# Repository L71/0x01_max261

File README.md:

0x01_max261
===========

This Maxim Max261 based Eurorack filter module is making this filter IC useful
for audio processing in a standard 16HP Eurorack synth module. 
The IC is a dual filter and each filter is independently controlled using front
panel knobs and control voltage inputs. The filter mode selection buttons provide
these filter types in each filter section:
Low pass, band pass, high pass, notch (lowpass+highpass mixed).
The maximum frequency range is logarithmic 30Hz-16.6KHz with the current firmware.

There are separate knobs and CV inputs for the frequency and resonance of each filter.
The resulting control voltages are read by an Atmel ATmega328 microcontroller that
is programming the max261 filter IC. It also provides the clock signals to
the filter sections. 

The output of filter A is connected to the input of filter B if no cables are inserted.

The filter IC used is not built for use in musical instruments. It suffers from some
clock signal bleed (+- 4mV at 50x the filter cutoff frequency) and due to its switched
capacitor technology it behaves somewhat like a sampled system and has a Nyquist
frequency at 25x the filter cutoff frequency. The clock bleed will be audible in LP
mode with low cutoff values if the filter is the last unit in the signal chain.
Make sure to read the Maxim max261 data sheets if you plan to build one of these. 

The microcontroller source code is released under the GPL v3.0 license. 
The PCBs and front panel drawings are released under the Creative Commons CC BY-SA 4.0 license.

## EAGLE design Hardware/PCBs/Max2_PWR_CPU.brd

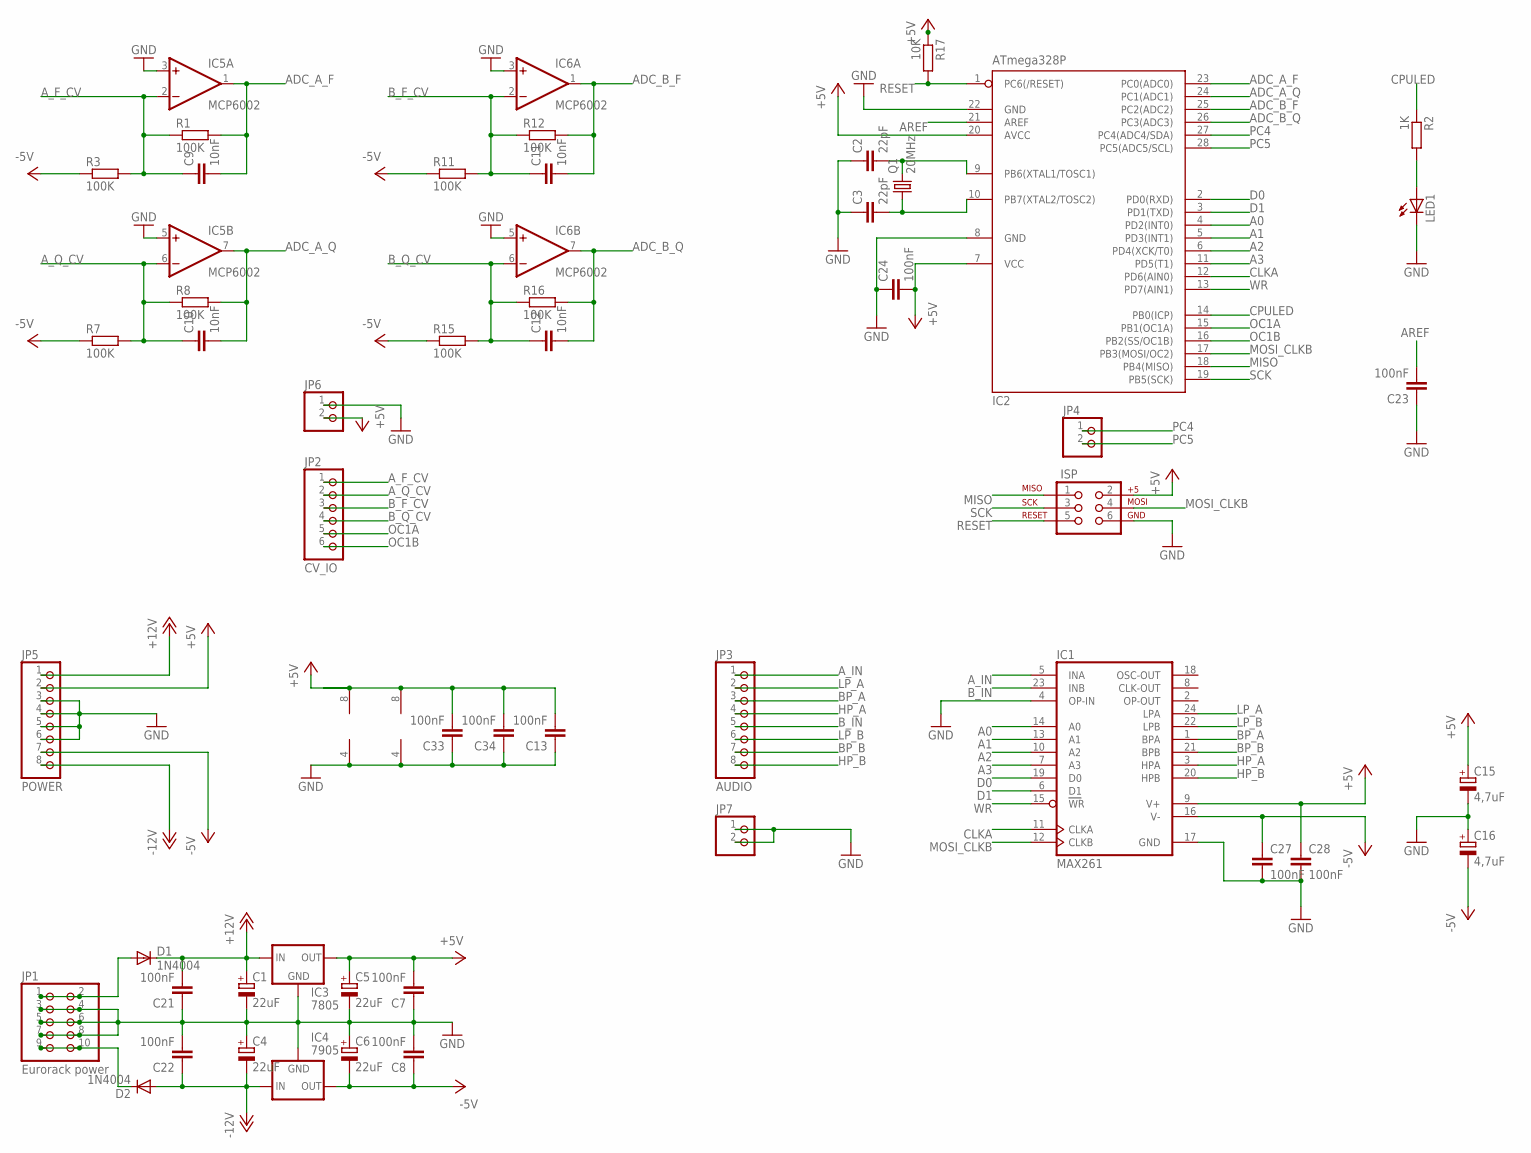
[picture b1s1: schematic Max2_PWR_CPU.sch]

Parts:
C1, C4, C5, C6: 22uF; E2,5-7
C2, C3: 22pF; C025-025X050
C7, C8, C13, C21, C22, C23, C24, C27, C28, C33, C34: 100nF; C025-025X050
C9, C10, C11, C12: 10nF; C025-025X050
C15, C16: 4,7uF; E2,5-6
D1, D2: 1N4004; DO41-10
IC1: MAX261; DIL24-3
IC2: ATmega328P; DIL28-3
IC3: 7805; 78XXS
IC4: 7905; 79XXS
IC5, IC6: MCP6002; DIL08
ISP: AVR_SPI_PRG_6NS; 2X3-NS
JP1: Eurorack power; 2X05
JP2: CV_IO; 1X06
JP3: AUDIO; 1X08
JP4, JP6, JP7: PINHD-1X2; 1X02
JP5: POWER; 1X08
LED1: LED3MM
Q1: 20MHz; HC49/S
R1, R3, R7, R8, R11, R12, R15, R16: 100K; 0207/2V
R2: 1K; 0207/2V
R17: 10K; 0207/2V

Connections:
+5V: C5.+, C7.2, C13.2, C15.+, C24.2, C28.1, C33.2, C34.2, IC1.9 (V+), IC2.7 (VCC), IC2.20 (AVCC), IC3.OUT, IC5.8 (V+), IC6.8 (V+), ISP.2, JP5.2, JP6.2, R17.1
+12V: C1.+, C21.2, D1.C, IC3.IN, JP5.1
-5V: C6.-, C8.1, C16.-, C27.1, IC1.16 (V-), IC4.OUT, JP5.7, R3.1, R7.1, R11.1, R15.1
-12V: C4.-, C22.1, D2.A, IC4.IN, JP5.8
A0: IC1.14 (A0), IC2.4 (PD2(INT0))
A1: IC1.13 (A1), IC2.5 (PD3(INT1))
A2: IC1.10 (A2), IC2.6 (PD4(XCK/T0))
A3: IC1.7 (A3), IC2.11 (PD5(T1))
ADC_A_F: C9.2, IC2.23 (PC0(ADC0)), IC5.1 (OUT), R1.2
ADC_A_Q: C10.2, IC2.24 (PC1(ADC1)), IC5.7 (OUT), R8.2
ADC_B_F: C11.2, IC2.25 (PC2(ADC2)), IC6.1 (OUT), R12.2
ADC_B_Q: C12.2, IC2.26 (PC3(ADC3)), IC6.7 (OUT), R16.2
AREF: C23.2, IC2.21 (AREF)
A_F_CV: C9.1, IC5.2 (-IN), JP2.1, R1.1, R3.2
A_IN: IC1.5 (INA), JP3.1
A_Q_CV: C10.1, IC5.6 (-IN), JP2.2, R7.2, R8.1
BP_A: IC1.1 (BPA), JP3.3
BP_B: IC1.21 (BPB), JP3.7
B_F_CV: C11.1, IC6.2 (-IN), JP2.3, R11.2, R12.1
B_IN: IC1.23 (INB), JP3.5
B_Q_CV: C12.1, IC6.6 (-IN), JP2.4, R15.2, R16.1
CLKA: IC1.11 (CLKA), IC2.12 (PD6(AIN0))
CPULED: IC2.14 (PB0(ICP)), R2.1
D0: IC1.19 (D0), IC2.2 (PD0(RXD))
D1: IC1.6 (D1), IC2.3 (PD1(TXD))
GND: C1.-, C2.1, C3.1, C4.+, C5.-, C6.+, C7.1, C8.2, C13.1, C15.-, C16.+, C21.1, C22.2, C23.1, C24.1, C27.2, C28.2, C33.1, C34.1, IC1.4 (OP-IN), IC1.17 (GND), IC2.8 (GND), IC2.22 (GND), IC3.GND, IC4.GND, IC5.3 (+IN), IC5.4 (V-), IC5.5 (+IN), IC6.3 (+IN), IC6.4 (V-), IC6.5 (+IN), ISP.6, JP1.3, JP1.4, JP1.5, JP1.6, JP1.7, JP1.8, JP5.3, JP5.4, JP5.5, JP5.6, JP6.1, JP7.1, JP7.2, LED1.K (C)
HP_A: IC1.3 (HPA), JP3.4
HP_B: IC1.20 (HPB), JP3.8
LP_A: IC1.24 (LPA), JP3.2
LP_B: IC1.22 (LPB), JP3.6
MISO: IC2.18 (PB4(MISO)), ISP.1
MOSI_CLKB: IC1.12 (CLKB), IC2.17 (PB3(MOSI/OC2)), ISP.4
unnamed: C2.2, IC2.9 (PB6(XTAL1/TOSC1)), Q1.2
unnamed: C3.2, IC2.10 (PB7(XTAL2/TOSC2)), Q1.1
unnamed: LED1.A, R2.2
unnamed: D1.A, JP1.1, JP1.2
unnamed: D2.C, JP1.9, JP1.10
OC1A: IC2.15 (PB1(OC1A)), JP2.5
OC1B: IC2.16 (PB2(SS/OC1B)), JP2.6
PC4: IC2.27 (PC4(ADC4/SDA)), JP4.1
PC5: IC2.28 (PC5(ADC5/SCL)), JP4.2
RESET: IC2.1 (PC6(/RESET)), ISP.5, R17.2
SCK: IC2.19 (PB5(SCK)), ISP.3
WR: IC1.15 (WR), IC2.13 (PD7(AIN1))

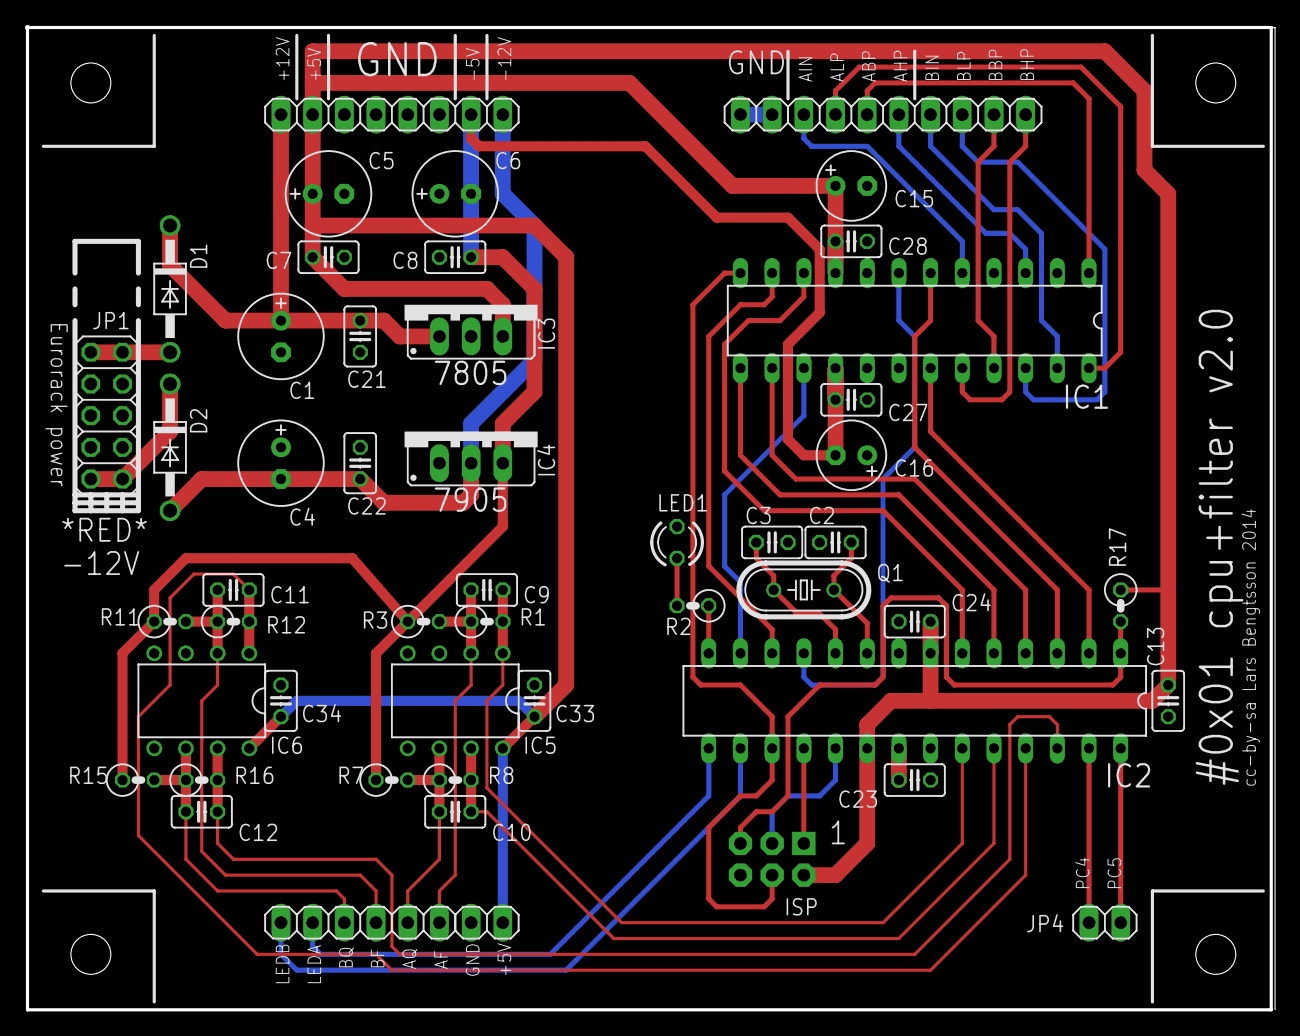
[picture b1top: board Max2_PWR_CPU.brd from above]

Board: 2 copper layers, 99.7 x 78.7 mm, 51 parts (0 on the bottom side), 44 nets.

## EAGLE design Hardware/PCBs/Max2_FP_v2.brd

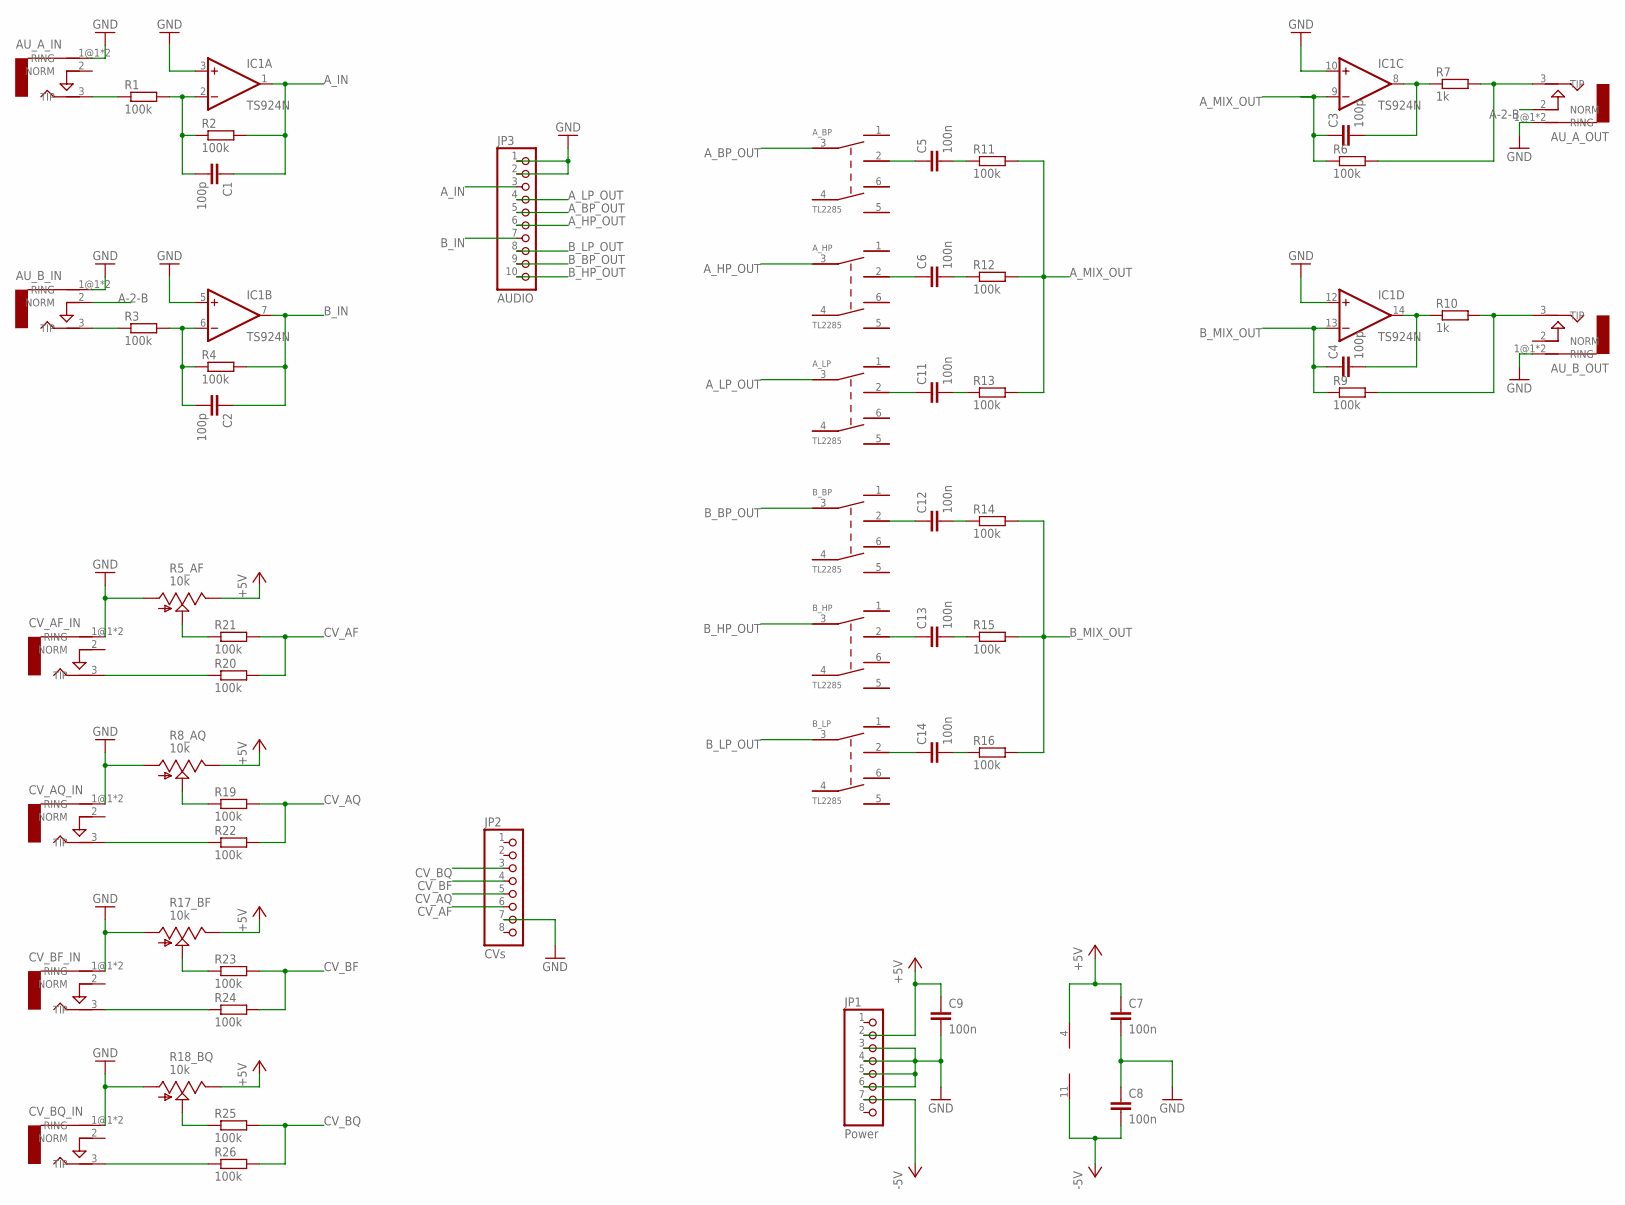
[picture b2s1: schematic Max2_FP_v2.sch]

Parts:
AU_A_IN: AUDIO-JACKERTHENVAR; ERTHENVAR-JACK
AU_A_OUT: AUDIO-JACKERTHENVAR; ERTHENVAR-JACK
AU_B_IN: AUDIO-JACKERTHENVAR; ERTHENVAR-JACK
AU_B_OUT: AUDIO-JACKERTHENVAR; ERTHENVAR-JACK
A_BP: TL2285; TL2285_PCB
A_HP: TL2285; TL2285_PCB
A_LP: TL2285; TL2285_PCB
B_BP: TL2285; TL2285_PCB
B_HP: TL2285; TL2285_PCB
B_LP: TL2285; TL2285_PCB
C1, C2, C3, C4: 100p; C025-025X050
C5, C6, C11, C12, C13, C14: 100n; C050-025X075
C7, C8, C9: 100n; C025-025X050
CV_AF_IN: AUDIO-JACKERTHENVAR; ERTHENVAR-JACK
CV_AQ_IN: AUDIO-JACKERTHENVAR; ERTHENVAR-JACK
CV_BF_IN: AUDIO-JACKERTHENVAR; ERTHENVAR-JACK
CV_BQ_IN: AUDIO-JACKERTHENVAR; ERTHENVAR-JACK
IC1: TS924N; DIL14
JP1: Power; 1X08
JP2: CVs; 1X08
JP3: AUDIO; 1X10
R1, R2, R3, R4, R6, R9, R11, R12, R13, R14, R15, R16, R19, R20, R21, R22, R23, R24, R25, R26: 100k; 0207/2V
R5_AF, R8_AQ, R17_BF, R18_BQ: 10k; ALPS_POT_VERTICAL
R7, R10: 1k; 0207/2V

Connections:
+5V: C7.1, C9.1, IC1.4 (V+), JP1.2, R5_AF.P$1 (E), R8_AQ.P$1 (E), R17_BF.P$1 (E), R18_BQ.P$1 (E)
-5V: C8.2, IC1.11 (V-), JP1.7
A-2-B: AU_A_OUT.2 (NORM), AU_B_IN.2 (NORM)
A_BP_OUT: A_BP.3, JP3.5
A_HP_OUT: A_HP.3, JP3.6
A_IN: C1.1, IC1.1 (OUT), JP3.3, R2.2
A_LP_OUT: A_LP.3, JP3.4
A_MIX_OUT: C3.1, IC1.9 (-IN), R6.1, R11.2, R12.2, R13.2
B_BP_OUT: B_BP.3, JP3.9
B_HP_OUT: B_HP.3, JP3.10
B_IN: C2.1, IC1.7 (OUT), JP3.7, R4.2
B_LP_OUT: B_LP.3, JP3.8
B_MIX_OUT: C4.1, IC1.13 (-IN), R9.1, R14.2, R15.2, R16.2
CV_AF: JP2.6, R20.2, R21.2
CV_AQ: JP2.5, R19.2, R22.2
CV_BF: JP2.4, R23.2, R24.2
CV_BQ: JP2.3, R25.2, R26.2
GND: AU_A_IN.1@1 (RING), AU_A_IN.1@2 (RING), AU_A_OUT.1@1 (RING), AU_A_OUT.1@2 (RING), AU_B_IN.1@1 (RING), AU_B_IN.1@2 (RING), AU_B_OUT.1@1 (RING), AU_B_OUT.1@2 (RING), C7.2, C8.1, C9.2, CV_AF_IN.1@1 (RING), CV_AF_IN.1@2 (RING), CV_AQ_IN.1@1 (RING), CV_AQ_IN.1@2 (RING), CV_BF_IN.1@1 (RING), CV_BF_IN.1@2 (RING), CV_BQ_IN.1@1 (RING), CV_BQ_IN.1@2 (RING), IC1.3 (+IN), IC1.5 (+IN), IC1.10 (+IN), IC1.12 (+IN), JP1.3, JP1.4, JP1.5, JP1.6, JP2.7, JP3.1, JP3.2, R5_AF.P$3 (A), R8_AQ.P$3 (A), R17_BF.P$3 (A), R18_BQ.P$3 (A)
unnamed: A_BP.2, C5.1
unnamed: AU_A_IN.3 (TIP), R1.1
unnamed: C1.2, IC1.2 (-IN), R1.2, R2.1
unnamed: C3.2, IC1.8 (OUT), R7.1
unnamed: AU_A_OUT.3 (TIP), R6.2, R7.2
unnamed: C5.2, R11.1
unnamed: C2.2, IC1.6 (-IN), R3.2, R4.1
unnamed: AU_B_IN.3 (TIP), R3.1
unnamed: C6.2, R12.1
unnamed: A_HP.2, C6.1
unnamed: A_LP.2, C11.1
unnamed: C11.2, R13.1
unnamed: C4.2, IC1.14 (OUT), R10.1
unnamed: AU_B_OUT.3 (TIP), R9.2, R10.2
unnamed: B_BP.2, C12.1
unnamed: R5_AF.P$2 (S), R21.1
unnamed: C12.2, R14.1
unnamed: CV_AF_IN.3 (TIP), R20.1
unnamed: CV_BQ_IN.3 (TIP), R26.1
unnamed: B_HP.2, C13.1
unnamed: CV_AQ_IN.3 (TIP), R22.1
unnamed: R8_AQ.P$2 (S), R19.1
unnamed: R17_BF.P$2 (S), R23.1
unnamed: C13.2, R15.1
unnamed: CV_BF_IN.3 (TIP), R24.1
unnamed: R18_BQ.P$2 (S), R25.1
unnamed: B_LP.2, C14.1
unnamed: C14.2, R16.1

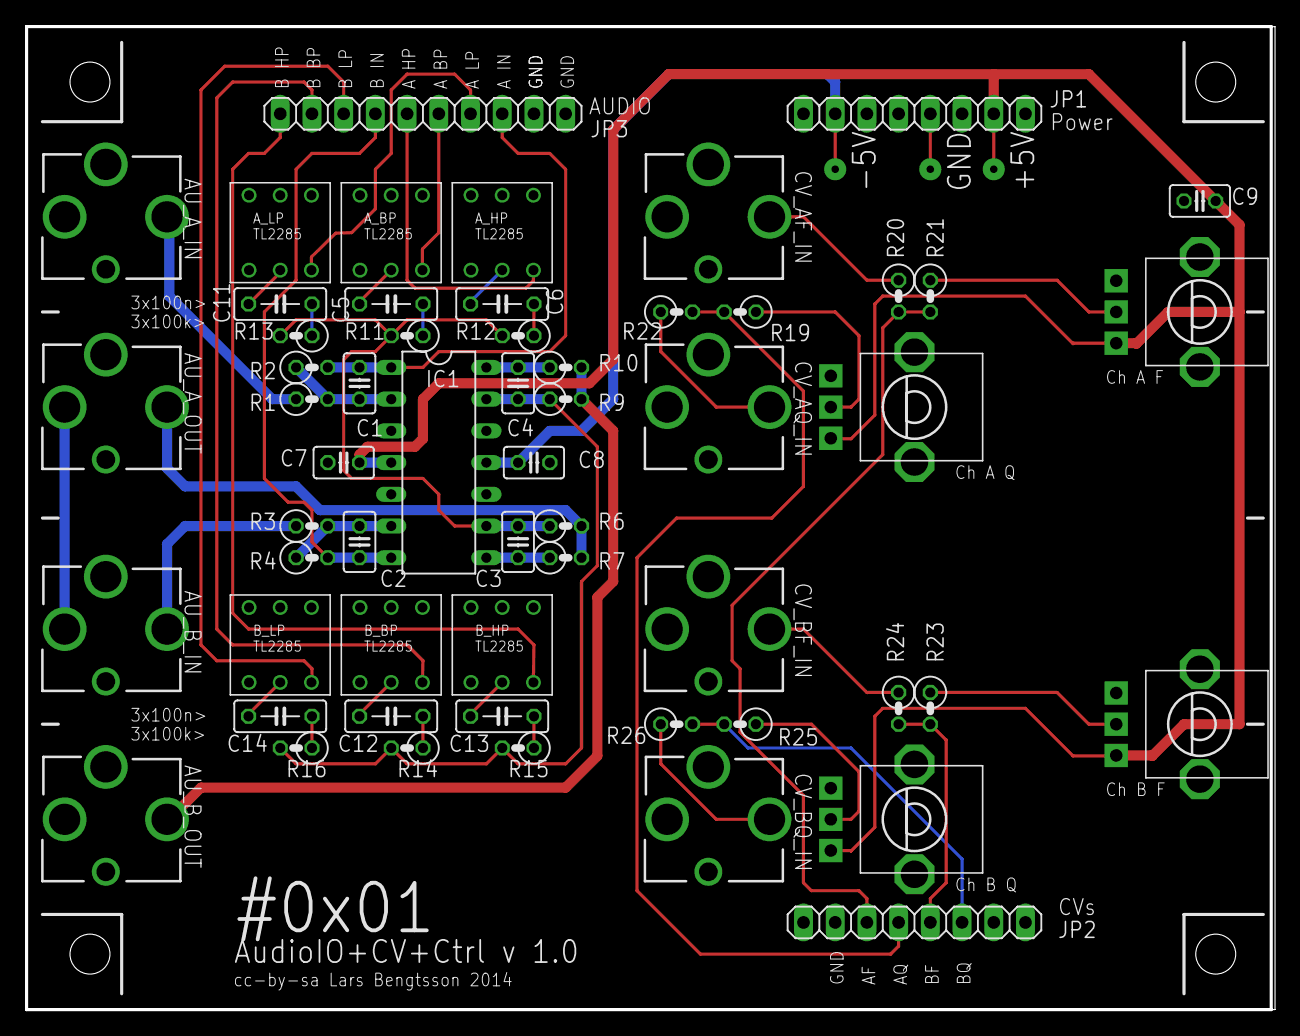
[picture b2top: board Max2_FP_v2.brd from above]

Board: 2 copper layers, 100.0 x 78.7 mm, 57 parts (0 on the bottom side), 46 nets.

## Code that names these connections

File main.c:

#define F_CPU 20000000UL

#include <avr/io.h>
#include <util/delay.h>
#include <avr/interrupt.h>

#include "adc.h"
#include "filterclock.h"
#include "max261.h"


void setup_leftover_pins() {
	// enable pull-up resistors on PC4 and PC5
	PORTC |= 0x30;
	
	// same on PB1,PB2 (OC1A, OC1B, LED status pins originally)
	PORTB |= 0x06;
}


int main() {

    // PB0 = output for I'm Alive Blink
    DDRB |= (1<<PB0);

	// blink PB0 LED once.
	PORTB |= 0b00000001;
	_delay_ms(200);
	PORTB &= 0b11111110;
	_delay_ms(200);
	PORTB |= 0b00000001;

	// setup & run system timer
	// setup_system_timer(); // DISABLED.
	
	// start frequency generator timers
	setup_f_timer();

	// initialize filter hw
	init_max261();
	
	// set filter modes (See max261 data sheet for details)
	// 1:  LP, BP, N
	// 2:  LP, BP, N (other characteristics)
	// 3:  LP, BP, HP
	// 4:  LP, BP, AP
	set_mode(2, 0);	// Filter A mode 3
	set_mode(2, 1);	// Filter B mode 3
	max261_write_f(1, 0);	// preset filter A F
	max261_write_f(1, 1);	// preset filter B F
	
	// do something with leftover IO pins
	setup_leftover_pins();
	
	// launch ADC conversions
	setup_adc();
	run_adc_timer();

    // Enable interrupts for all. GO! =)
    SREG |= 0x80 ;
	
    // main loop
    while ( 1 )  {
		PORTB |= 0b00000001;
        _delay_ms(2000);
		PORTB &= 0b11111110;
		_delay_ms(2000);
    }
  
}

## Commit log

2014-12-07 Upload of final versions for this hardware.
2014-12-07 Added PCB files.
2014-12-07 Added panel file .svg + Ponoko upload file.
2014-12-07 Added BOM files.
2014-12-07 Added info on dev environment.
2014-12-08 Fixed error in filter mode description.

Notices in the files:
Hardware/PCBs/Max2_FP_v2.brd:
cc-by-sa Lars Bengtsson 2014
